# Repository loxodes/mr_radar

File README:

mr_radar
=============

mr_radar is an in development open hardware frequency modulated continuous wave radar.

It is a radar altimeter for remote control quad-rotor helicopters and UAVs.
Eventually, it may be capable of radar imaging.

One of the goals of this project is to be easily reproducible and inexpensive.
All of the microwave components are available online from manufacturers or resellers like DigiKey, Allied Electronics, or Mini-Circuits. I have avoided using expensive components like circulators or SAW delay lines, even though they sound like fun. No chips with exposed pads are used, it is possible to assemble the boards with a soldering iron. All of the printed circuit boards are intended for plain inexpensive FR4 (which means filtering is done using chip filters and lumped elements, not distributed elements) and could be purchased from inexpensive board houses such as seeedstudio or iteadstudio. (I have several spares of most boards, I am willing to mail them out in exchange for postage.)
Signal processing will be done on a STM32F4 microcontroller, the STM32F4-Discovery evaluation board is available for around twenty dollars. 

Several test boards have been created for this project:
- mr_radar_frogpond proved the VCO and preamplifier amplifier layout and schematic.
- mr_radar_platypus contains all the microwave components, and proved the mixer, splitter, and IF amplifier.
- mr_radar_patch_antenna proved the patch antenna layout (it matched ADS simulation!)
- mr_radar_sandbox did not work as expected, the through hole SMA connector did not perform well at 3.4 GHz (but the U.fl did!)
- mr_radar_trolley is an in-progress board with voltage regulators, a VCO driver amplifier, and a USB-USART chip
- mr_radar_sandcastle is an untested board to evaluate an alternate mixer, a power splitter, and a directional coupler.

Some measurements (s-parameters, noise figure measurements) are available in data/ 

Some software has been written for this project:
- stm32f4_dacramp_adcif contains the code for the STM32F4 to generate the VCO control signal and sample the IF, and some python code to grab data off the STM32F4 and test signal processing
- vco_correction is an attempt at a VCO non-linearity correction algorithm. It is untested on hardware (because it requires expensive delay lines)
- compression is an in-progress (class project for a data compression class) to do image compression on the radar images (on the microcontroller)

Board layout is done so using Cadsoft Eagle.
Diagrams are drawn using Dia.
Software is written in Matlab, Python, and C.

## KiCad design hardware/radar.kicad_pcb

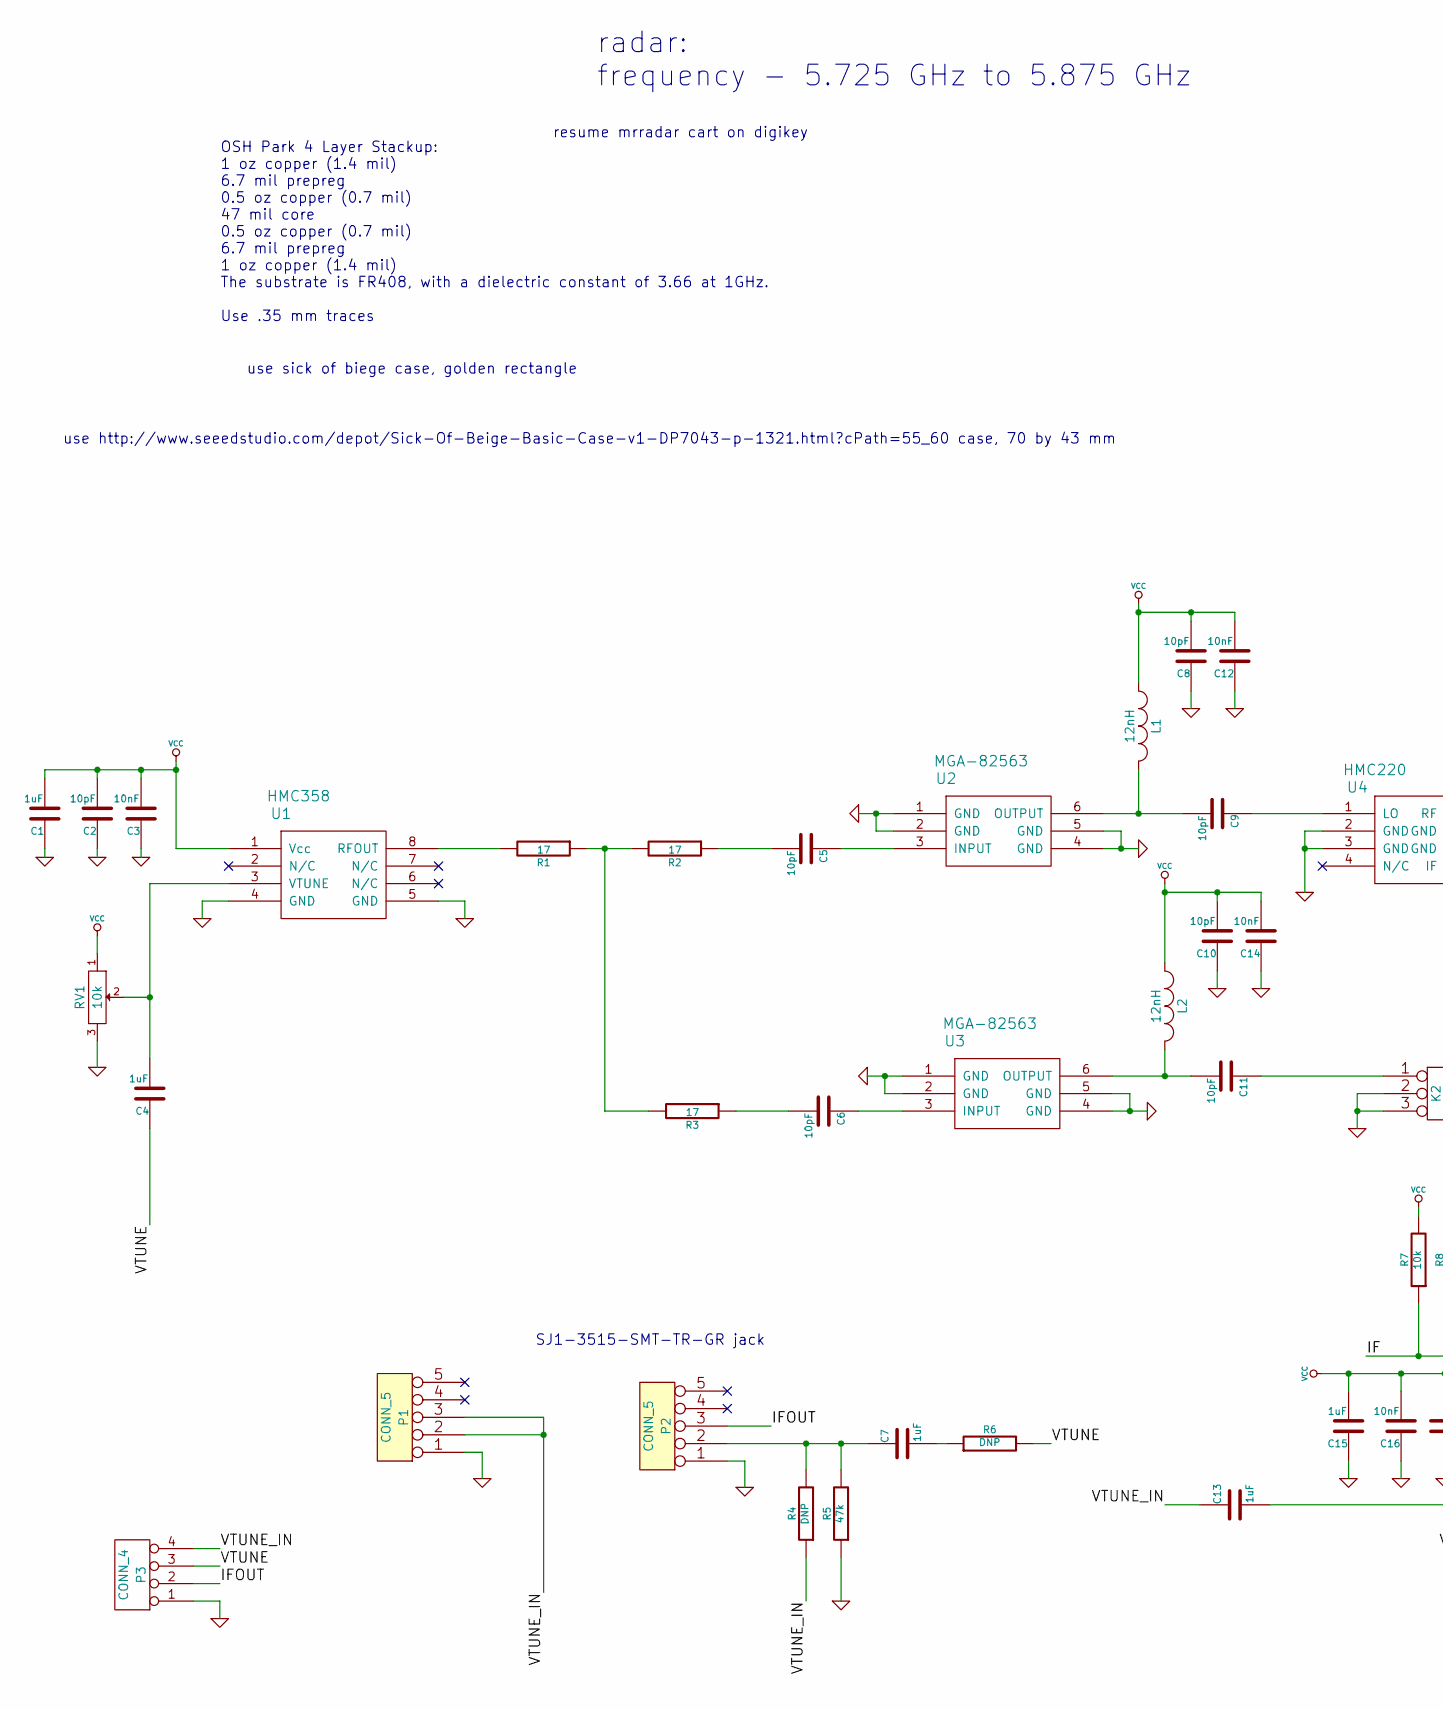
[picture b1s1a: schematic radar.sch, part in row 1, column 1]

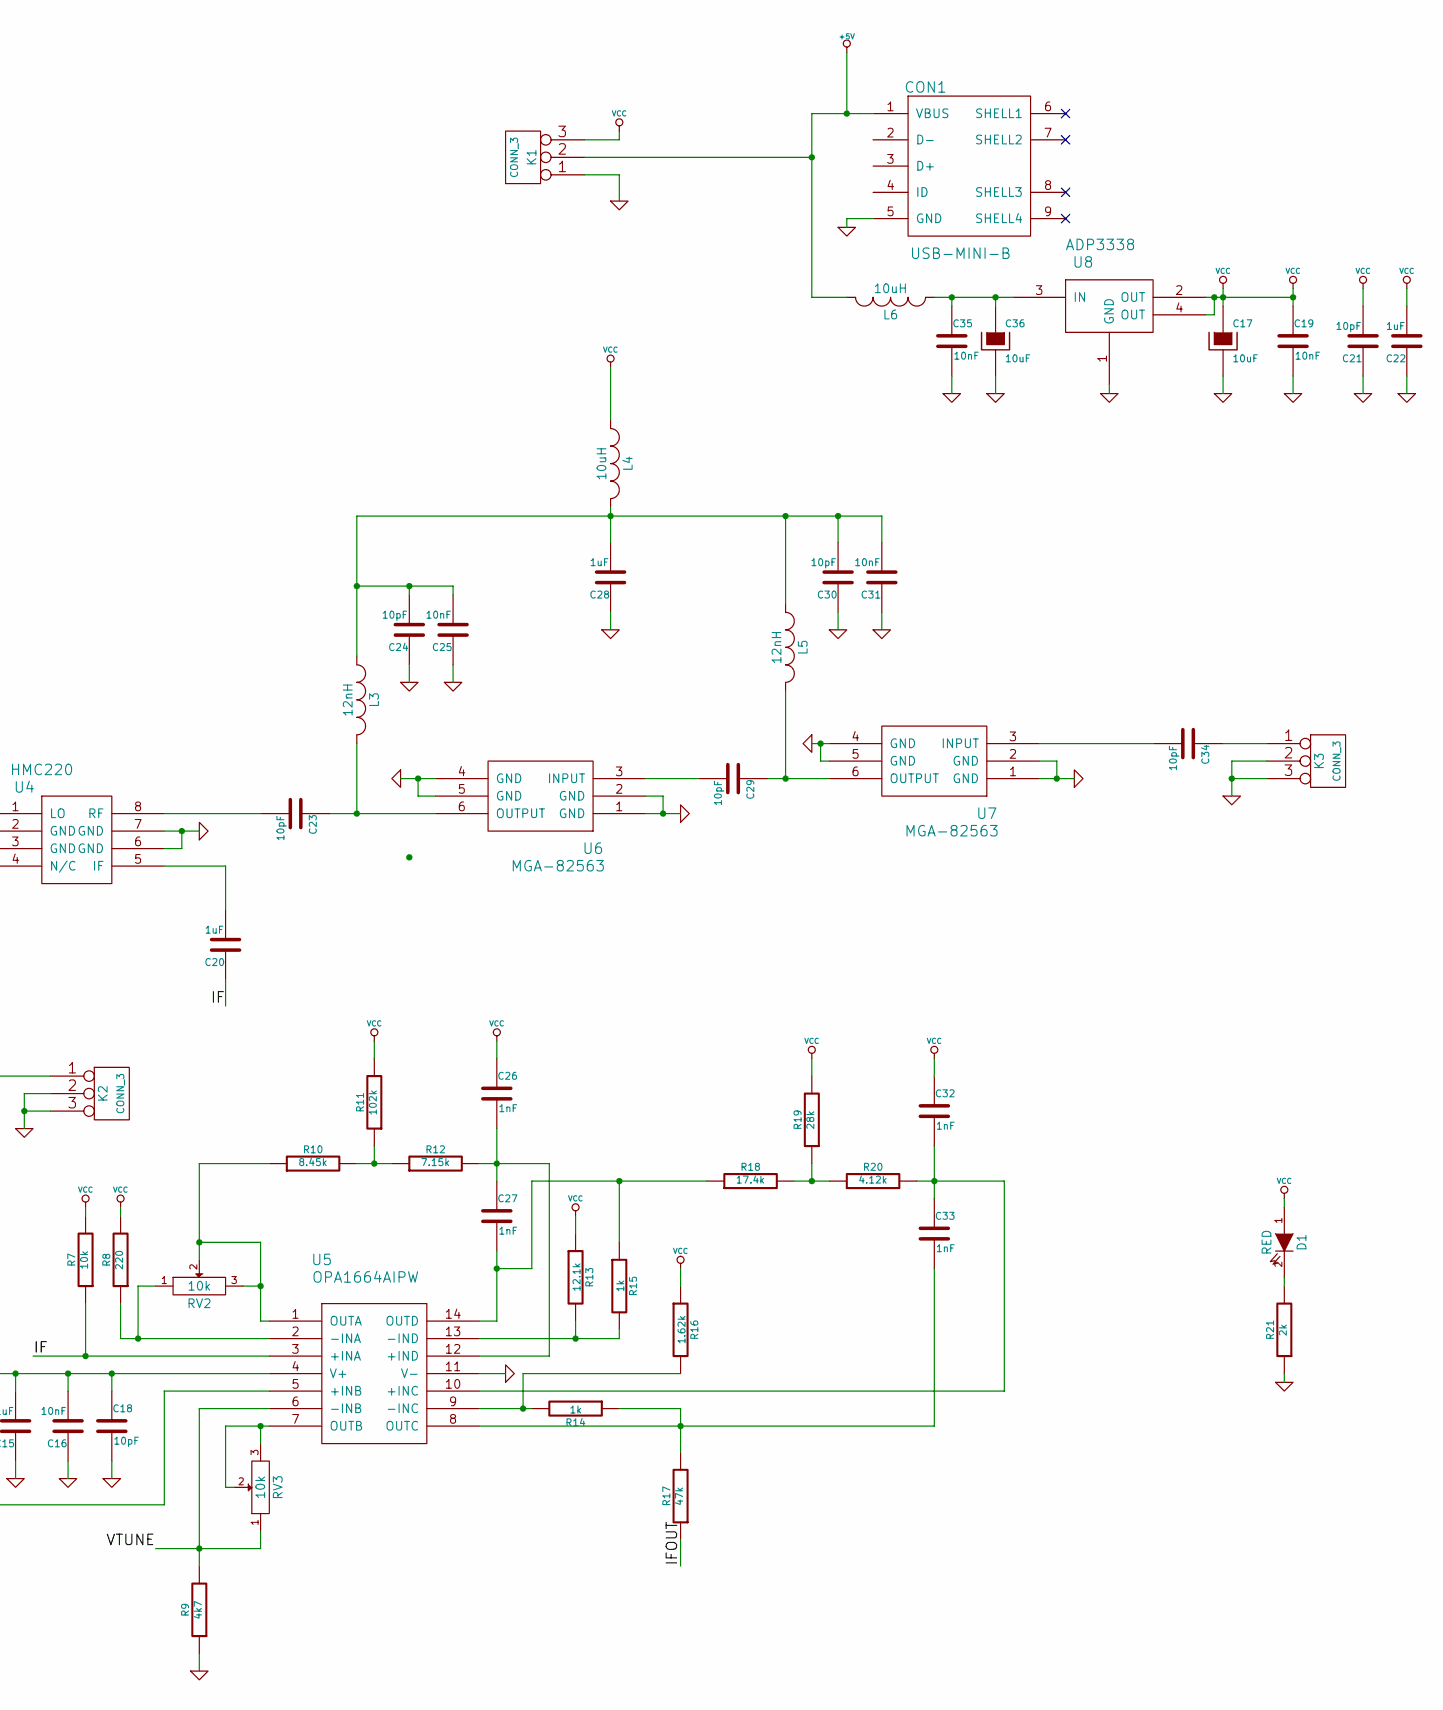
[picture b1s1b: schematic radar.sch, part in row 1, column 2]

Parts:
C1, C4, C7, C13, C15, C20, C22, C28: 1uF; SM0603
C2, C8, C10, C18, C21, C24, C30: 10pF; SM0603
C3, C12, C14, C16, C19, C25, C31, C35: 10nF; SM0603
C5, C6, C9, C11, C23, C29, C34: 10pF; SM0402
C17, C36: 10uF; SM1210
C26, C27, C32, C33: 1nF; SM0603
CON1: USB-MINI-B; USB_MINI_B
D1: RED; LED-0603
K1: CONN_3; PINHEAD1-3
K2, K3: CONN_3; U.FL-COAX
L1, L2, L3, L5: 12nH; SM0402
L4, L6: 10uH; SM1210
P1, P2: CONN_5; SJ1-351X-SMT
P3: CONN_4; SIL-4
R1, R2, R3: 17; SM0402
R4, R6: DNP; SM0603
R5, R17: 47k; SM0603
R7: 10k; SM0603
R8: 220; SM0603
R9: 4k7; SM0603
R10: 8.45k; SM0603
R11: 102k; SM0603
R12: 7.15k; SM0603
R13: 12.1k; SM0603
R14, R15: 1k; SM0603
R16: 1.62k; SM0603
R18: 17.4k; SM0603
R19: 28k; SM0603
R20: 4.12k; SM0603
R21: 2k; SM0603
RV1, RV2, RV3: 10k; Potentiometer_Bourns_3296Z_3-8Zoll_Angular_ScrewFront
U1: HMC358; MSOP-8
U2, U3, U6, U7: MGA-82563; sc70-6
U4: HMC220; MSOP-8
U5: OPA1664AIPW; TSSOP14
U8: ADP3338; SOT223

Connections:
+5V: CON1.1 (VBUS), K1.2 (PM), L6.2
/IF: C20.1, R7.1, U5.3 (+INA)
/IFOUT: P2.3, P3.2, R17.1
/VTUNE: C4.1, P3.3, R6.2, R9.2, RV3.1, U5.6 (-INB)
/VTUNE_IN: C13.1, P1.2, P1.3, P3.4, R4.1
GND: C1.1, C2.1, C3.1, C8.1, C10.1, C12.1, C14.1, C15.1, C16.1, C17.2, C18.2, C19.2, C21.1, C22.1, C24.1, C25.1, C28.1, C30.1, C31.1, C35.2, C36.2, CON1.5 (GND), K1.1, K2.2 (PM), K2.3, K3.2 (PM), K3.3, P1.1, P2.1, P3.1, R5.1, R9.1, R21.1, RV1.3, U1.4 (GND), U1.5 (GND), U2.1 (GND), U2.2 (GND), U2.4 (GND), U2.5 (GND), U3.1 (GND), U3.2 (GND), U3.4 (GND), U3.5 (GND), U4.2 (GND), U4.3 (GND), U4.6 (GND), U4.7 (GND), U5.11 (V-), U6.1 (GND), U6.2 (GND), U6.4 (GND), U6.5 (GND), U7.1 (GND), U7.2 (GND), U7.4 (GND), U7.5 (GND), U8.1 (GND); also elsewhere on the board
unnamed: C4.2, RV1.2, U1.3 (VTUNE)
unnamed: C5.1, U2.3 (INPUT)
unnamed: C5.2, R2.1
unnamed: C6.1, U3.3 (INPUT)
unnamed: C6.2, R3.1
unnamed: C7.1, P2.2, R4.2, R5.2
unnamed: C7.2, R6.1
unnamed: C9.1, U4.1 (LO)
unnamed: C9.2, L1.2, U2.6 (OUTPUT)
unnamed 15: C11.1, K2.1; also elsewhere on the board
unnamed: C11.2, L2.2, U3.6 (OUTPUT)
unnamed: C13.2, U5.5 (+INB)
unnamed: C20.2, U4.5 (IF)
unnamed: C23.1, L3.2, U6.6 (OUTPUT)
unnamed: C23.2, U4.8 (RF)
unnamed: C24.2, C25.2, C28.2, C30.2, C31.2, L3.1, L4.2, L5.1
unnamed: C26.2, C27.1, R12.2, U5.12 (+IND)
unnamed: C27.2, R15.1, R18.1, U5.14 (OUTD)
unnamed: C29.1, L5.2, U7.6 (OUTPUT)
unnamed: C29.2, U6.3 (INPUT)
unnamed: C32.2, C33.1, R20.2, U5.10 (+INC)
unnamed: C33.2, R14.1, R17.2, U5.8 (OUTC)
unnamed 28: C34.1, K3.1; also elsewhere on the board
unnamed: C34.2, U7.3 (INPUT)
unnamed: C35.1, C36.1, L6.1, U8.3 (IN)
unnamed: D1.2 (K), R21.2
unnamed: R1.1, R2.2, R3.2
unnamed: R1.2, U1.8 (RFOUT)
unnamed: R8.1, RV2.1, U5.2 (-INA)
unnamed: R10.1, RV2.2, RV2.3, U5.1 (OUTA)
unnamed: R10.2, R11.1, R12.1
unnamed: R13.2, R15.2, U5.13 (-IND)
unnamed: R14.2, R16.2, U5.9 (-INC)
unnamed: R18.2, R19.1, R20.1
unnamed: RV3.2, RV3.3, U5.7 (OUTB)
VCC: C1.2, C2.2, C3.2, C8.2, C10.2, C12.2, C14.2, C15.2, C16.2, C17.1, C18.1, C19.1, C21.2, C22.2, C26.1, C32.1, D1.1 (A), K1.3, L1.1, L2.1, L4.1, R7.2, R8.2, R11.2, R13.1, R16.1, R19.2, RV1.1, U1.1 (Vcc), U5.4 (V+), U8.2 (OUT), U8.4 (OUT)

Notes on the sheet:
radar: frequency - 5.725 GHz to 5.875 GHz
SJ1-3515-SMT-TR-GR jack
resume mrradar cart on digikey
OSH Park 4 Layer Stackup: 1 oz copper (1.4 mil) 6.7 mil prepreg 0.5 oz copper (0.7 mil) 47 mil core 0.5 oz copper (0.7 mil) 6.7 mil prepreg 1 oz copper (1.4 mil) The substrate is FR408, with a dielectric constant of 3.66 at 1GHz. Use .35 mm traces
use sick of biege case, golden rectangle
use http://www.seeedstudio.com/depot/Sick-Of-Beige-Basic-Case-v1-DP7043-p-1321.html?cPath=55_60 case, 70 by 43 mm

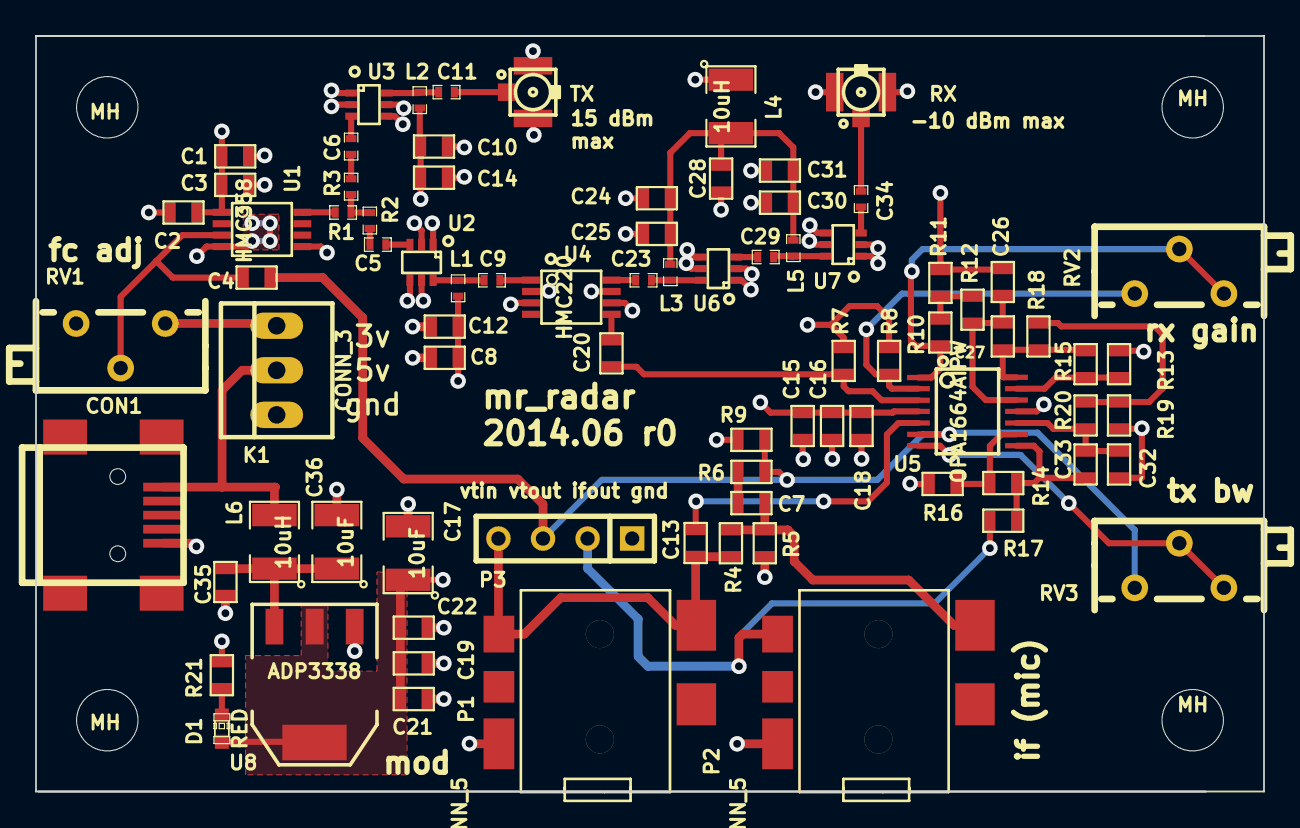
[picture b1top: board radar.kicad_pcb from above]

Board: 4 copper layers, 70.0 x 43.1 mm, 86 parts (0 on the bottom side), 42 nets.

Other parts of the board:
MH: MountingHole_3-5mm_RevA_Date21Jun2010; MountingHole_3-5mm
MH#2, MH#3, MH#4: MountingHole_3-5mm_RevA_Date21Jun2010; MountingHole_3-5mm
RX: CONN_3; U.FL-COAX
TX: CONN_3; U.FL-COAX

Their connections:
GND: RX.2, RX.3, TX.2, TX.3; also elsewhere on the board
unnamed 15: TX.1; also elsewhere on the board
unnamed 28: RX.1; also elsewhere on the board

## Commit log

2011-09-15 added eagle library with vco, balun, and quad demod
2011-09-15 added warning to readme.
2011-09-15 rough block diagram schematic of mr radar
2011-09-16 added variable gain amplifier to mr_radar library, started amplfier setup. I'll need to make a breakout board for the amp to figure out input/output matching..
2011-09-16 draft of trl cal/amplifier/antenna test board
2011-09-16 removed temp files
2011-09-16 added vco to test board
2011-09-16 fixed some drc errors: removed overlapping drills and increased to 6mil minimum spacing where possible
2011-09-16 fixed soldermask errors, added more via staples
2011-09-17 added r0 gerbers for mr radar sandbox, boards should arrive in a few weeks
2011-09-17 added directional coupler to library
2011-09-17 finished quad demod schematic, added antialiasing filter
2011-09-18 added headers vtune, I&Q outputs, supply voltage
2011-09-18 started on sandcastle - coupler, antialiasingfilter, baseband amplifier, and balun test board (maybe mixer too)
2011-09-19 removed antialiasing filter, started on layout
2011-09-19 layout of amplifier
2011-09-20 finished component placement and initial layout of sandcastle
2011-09-23 finished sandcastle layout
2011-10-18 started fmcw MATLAB simulation for vco nonlinearity correction
2011-10-18 added visualization of output
2011-10-19 added test file
2011-10-19 fixed mixer filter, added comments
2011-10-21 added fft output visualization
2011-10-27 added frogpond, 31mil routed fr4 edge launch sma connector amplifier and vco test board
2011-11-01 changed variable names to reflect proper domains..
2011-11-16 added minicircuits smd mixer and splitter
2011-11-16 added mixer/amp/splitter test board
2011-11-16 added messy broken LO output amplifier
2011-11-16 added u.FL testpoints on mixer and splitter, placed all components except LO driver amp
2011-11-16 simple analytic version of first few steps of algoritm working..
2011-11-16 placed lo driver
2011-11-17 layout of rx and lo amp
2011-11-17 partial layout of tx path
2011-11-17 finished first pass of layout. proper stiching vias and optimization remain..
2011-11-17 unfurled layout to larger board
2011-11-18 top ground planes finished
2011-11-24 added heavily via'ed platypus test board
2011-12-02 fixed then broke vco phase noise correction
2011-12-05 phase error detection in matlab simulation sorta works, added ramp vco error model
2011-12-07 properly finding phase errror in vco correction with reasonable assumptions. ~order of magnitude resolution increase for gaussian phase noise model
2011-12-07 updated variable name to reflect sane reality
2011-12-07 updated comments
2011-12-12 cleaned up vco simulation code
2011-12-23 updated layout of radar
2011-12-23 removed temp files..
2012-02-01 mr radar platypus test board ready for manufacturing
2012-02-01 removed some intermediate files
2012-02-04 added patch ~3.4GHz patch antenna (to be milled on campus)
2012-02-05 added component values to schematic, added silkscreen layer
2012-02-06 increased size of u.fl test point jumpers. attached gerbers of r0, sent for manufacturing
2012-02-16 added measured s2p of patch antenna (matches simulation! http://kl1xf.org/1329427704.png), now to optimize it..
2012-02-27 vna and spectrum anayzer measurements of mr_radar_platypus. it works
2012-03-07 added if amp and antialiasing filter values and LTSpice simulation, changed package sizes for rx amp decoupling capacitors, updated silkscreen with proper supply voltages
2012-03-11 added work in progress stm32f4 ramp generator/adc
2012-03-11 added python script to visualize radar output
2012-03-11 improved python/stm serial sync, fixed problems with repeated conversions
2012-03-11 added control of radar samples over serial port
2012-03-12 added bus pirate support to adc_grab (much faster sample uploading..)
2012-03-13 added mr_radar_trolley, voltage regulator/usb to usart/vco driver amplifier board
2012-03-13 finished component placement draft on mr_radar_trolley
2012-03-13 added attempt at clutter removal
2012-03-13 finished mr_radar_trolley layout
2012-03-13 fixed README formatting
2012-03-13 gave README .md extention, maybe this will work..
2012-03-14 fixes to ft232rl layout and schematic, cleanup of silkscreen layer, sent for manufacturing
2012-03-15 added picture of mr_radar_platypus
2012-03-15 updated readme markdown syntax (maybe the image works now?)
2012-03-15 fixed link to image in README.md
2012-03-15 started work on data compression project, added code to read, display, and calculate the entropy of SRTM files
2012-03-20 added pulsed rf source test board
2012-03-20 finished silkscreen layer on mr_radar_pulser
2012-03-22 added LT5534 to library, mr_radar_pulser ready for manufacturing
2012-03-23 added ad4350 and adl5375 to eagle library
2012-03-26 added patch antenna (WLP.2450.25.4.A.02) to library, mr_radar_pulser sent for manufacturing
2012-04-16 added incomplete and untested JPEG-LS encoder
2012-04-16 RLE mode, updated README
2012-04-27 more work on JPEG-LS encoder, still incomplete
2012-04-27 JPEG-LS now runs, missing limited length golomb codes and probably other features
2012-04-28 more work on jpeg_ls, still almost certainly broken
2012-04-29 fixed bugs in limiting golomb codes and more, still broken
2012-04-29 fixed bugs with contex pixels
2012-04-29 fixed some bugs in run mode, still broken..
2012-04-29 fixed more run mode bugs..
2012-04-29 fixed bug with quantization
2012-04-29 removed some debugging code
2012-05-01 added (broken?) lossy JPEG-LS mode
2012-10-03 started work on mr_radar_ferret, and redesigned FMCW front end for 2.4 GHz with an integrated VCO, DAC, and ADC
2012-10-03 component placement complete on ferret, layout partially complete. silkscreen cleanup and amplifier grounds remain
2012-10-03 split adc front-end to another board, changed microstrip for 1.6mm thick board
2012-10-04 mr_radar_ferret r0, sent for manufacturing
2012-10-26 currently tested ferret r0, fixing a few bugs for the next revision, board layout of ferret now incomplete. isolation is much better than in platypus, but it is still a problem
2014-06-13 removed abandoned boards, added latest revision
2014-06-13 updated readme..
